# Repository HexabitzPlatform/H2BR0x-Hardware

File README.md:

# H2RB0x-Hardware
Hexabitz Single-Lead, Heart Rate Monitor Front End (based on AD8232) Module Hardware Design

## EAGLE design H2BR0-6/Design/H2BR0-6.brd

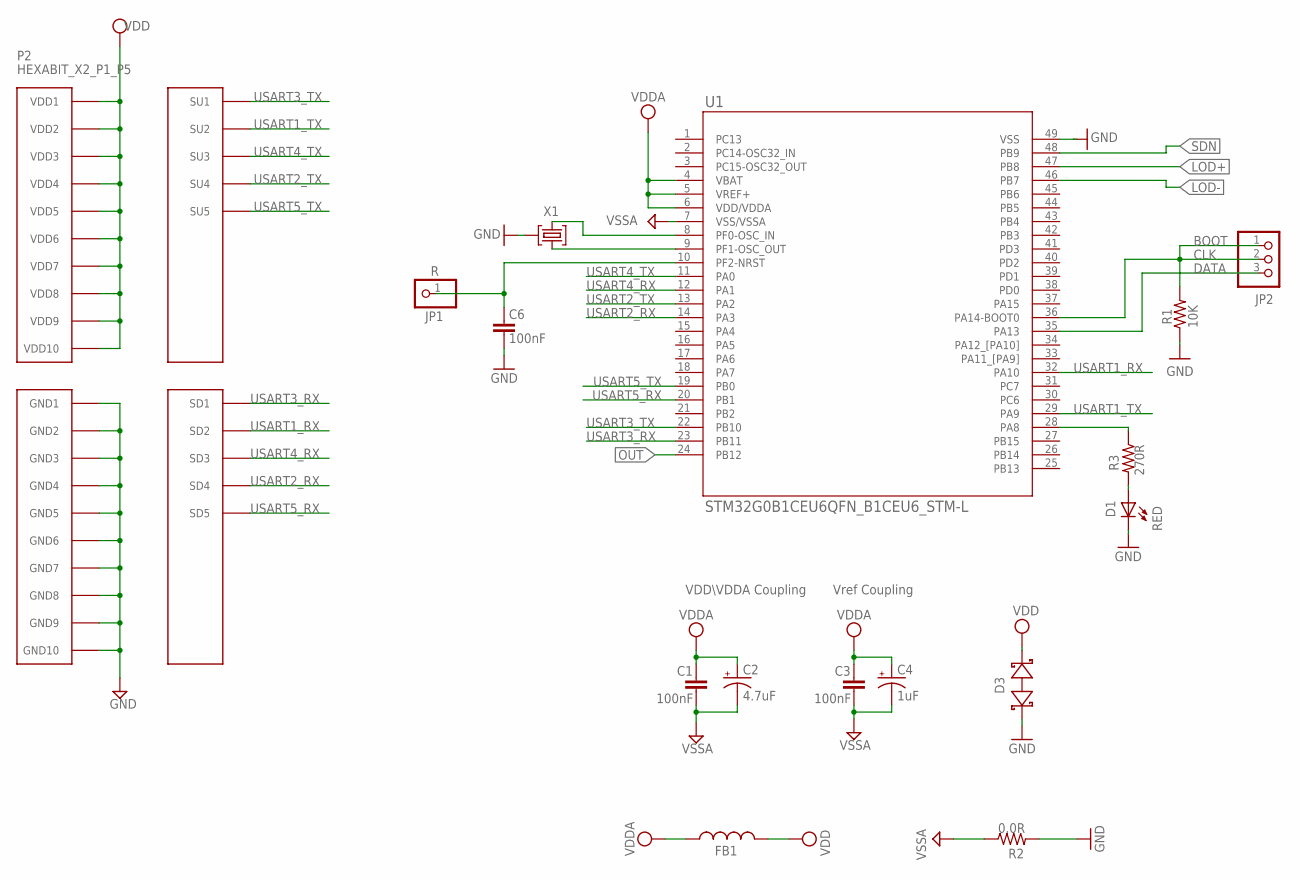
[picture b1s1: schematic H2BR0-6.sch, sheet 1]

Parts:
C1, C3, C6: 100nF; C-0603
C2: 4.7uF; C-0805-POL
C4: 1uF; C-0805-POL
D1: RED; VLMS1300-GS08; MPN VLMS1300-GS08
D3: BOURNS_CDSOD323-T03SCBOURNS_CDSOD323-T03SC_0_0; BOURNS_CDSOD323-T03SC_0
FB1: FB-0603
JP1: R; 1X01
JP2: PINHD-1X3; 1X03
P2: HEXABIT_X2_P1_P5; HEXABIT_17.32_X2_P1_P5
R1: 10K; R-0603
R2: 0.0R; R-0603
R3: 270R; R-0603
TRIMBLE-LOGO2: HEXA-LOGO
U1: STM32G0B1CEU6QFN_B1CEU6_STM-L; QFN_B1CEU6_STM-L
X1: XTALL_CSTCE8M00G52

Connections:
CLK: JP2.1, JP2.2, R1.2, U1.36 (PA14-BOOT0)
DATA: JP2.3, U1.35 (PA13)
GND: C6.2, D1.C, D3.1 (A), P2.PAD_PD11 (GND1), P2.PAD_PD12 (GND2), P2.PAD_PD13 (GND3), P2.PAD_PD14 (GND4), P2.PAD_PD15 (GND5), P2.PAD_PD16 (GND6), P2.PAD_PD17 (GND7), P2.PAD_PD18 (GND8), P2.PAD_PD19 (GND9), P2.PAD_PD20 (GND10), R1.1, R2.2, U1.49 (VSS), X1.P$2 (2)
LOD+: U1.47 (PB8); also elsewhere on the board
LOD-: U1.46 (PB7); also elsewhere on the board
unnamed: D1.A, R3.2
unnamed: R3.1, U1.28 (PA8)
unnamed: U1.9 (PF1-OSC_OUT), X1.P$1 (1)
unnamed: U1.8 (PF0-OSC_IN), X1.P$3 (3)
unnamed: C6.1, JP1.1, U1.10 (PF2-NRST)
OUT: U1.24 (PB12); also elsewhere on the board
SDN: U1.48 (PB9); also elsewhere on the board
USART1_RX: P2.PAD_PD2 (SD2), U1.32 (PA10)
USART1_TX: P2.PAD_PU2 (SU2), U1.29 (PA9)
USART2_RX: P2.PAD_PD4 (SD4), U1.14 (PA3)
USART2_TX: P2.PAD_PU4 (SU4), U1.13 (PA2)
USART3_RX: P2.PAD_PD1 (SD1), U1.23 (PB11)
USART3_TX: P2.PAD_PU1 (SU1), U1.22 (PB10)
USART4_RX: P2.PAD_PD3 (SD3), U1.12 (PA1)
USART4_TX: P2.PAD_PU3 (SU3), U1.11 (PA0)
USART5_RX: P2.PAD_PD5 (SD5), U1.20 (PB1)
USART5_TX: P2.PAD_PU5 (SU5), U1.19 (PB0)
VDD: D3.2 (C), FB1.2, P2.PAD_PU11 (VDD1), P2.PAD_PU12 (VDD2), P2.PAD_PU13 (VDD3), P2.PAD_PU14 (VDD4), P2.PAD_PU15 (VDD5), P2.PAD_PU16 (VDD6), P2.PAD_PU17 (VDD7), P2.PAD_PU18 (VDD8), P2.PAD_PU19 (VDD9), P2.PAD_PU20 (VDD10); also elsewhere on the board
VDDA: C1.1, C2.1 (+), C3.1, C4.1 (+), FB1.1, U1.4 (VBAT), U1.5 (VREF+), U1.6 (VDD/VDDA); also elsewhere on the board
VSSA: C1.2, C2.2 (-), C3.2, C4.2 (-), R2.1, U1.7 (VSS/VSSA); also elsewhere on the board

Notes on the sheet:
Vref Coupling
VDD\VDDA Coupling
BOOT

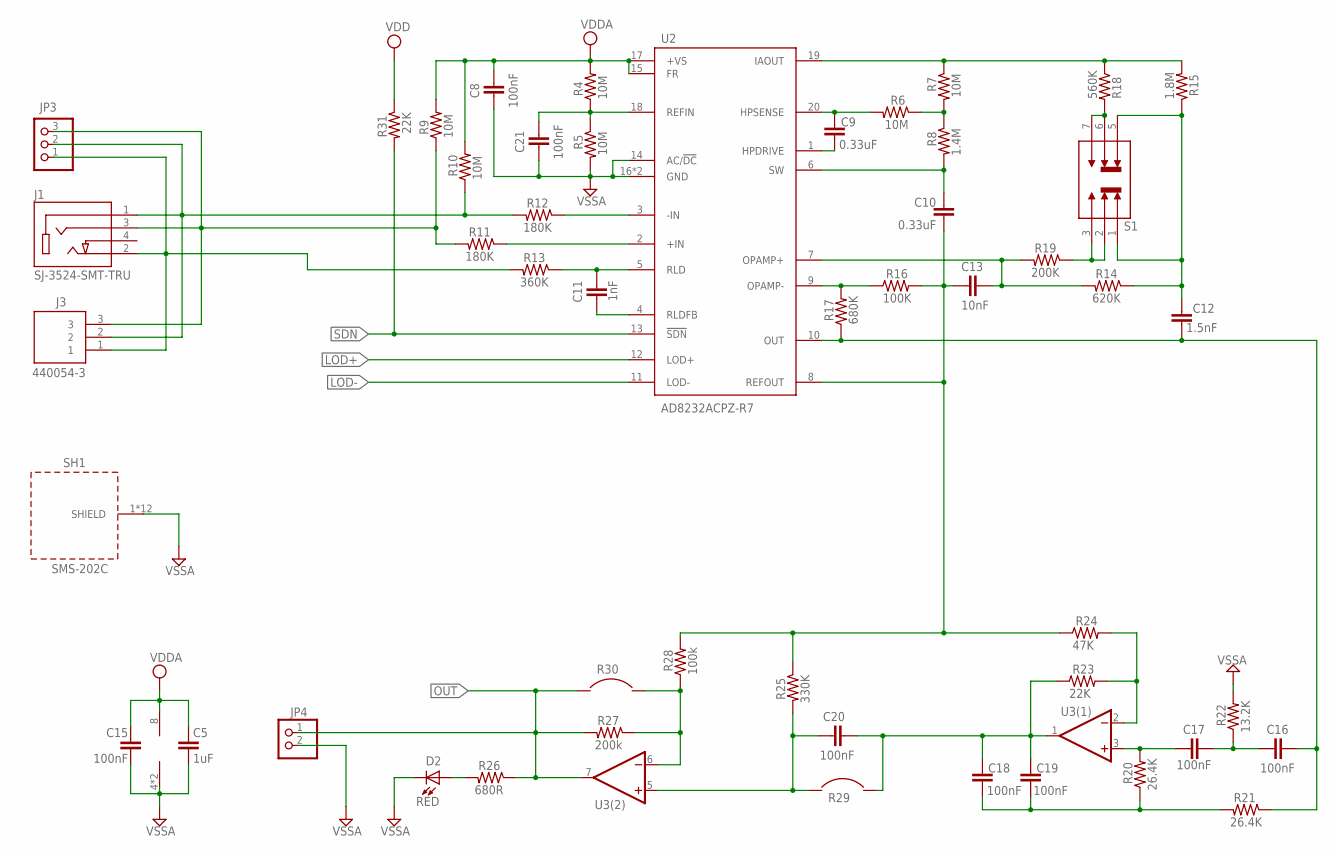
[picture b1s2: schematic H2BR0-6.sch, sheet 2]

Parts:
C5: 1uF; C-0402
C8, C15, C16, C17, C18, C19, C21: 100nF; C-0402
C9, C10: 0.33uF; C-0402
C11: 1nF; C-0402
C12: 1.5nF; C-0402
C13: 10nF; C-0402
C20: 100nF; C-0402; MPN GRM188R61A105KA61J
D2: RED; VLMS1300-GS08; MPN VLMS1300-GS08
J1: SJ-3524-SMT-TRU; CUI_SJ-3524-SMT
J3: 440054-3; SHDR3W50P0X200_1X3_800X470X635
JP3: PINHD-1X3; 1X03
JP4: PINHD-1X2(ROUND); 1X02
R4, R5, R6, R7, R9, R10: 10M; R-0402
R8: 1.4M; R-0402
R11, R12: 180K; R-0402
R13: 360K; R-0402
R14: 620K; R-0402
R15: 1.8M; R-0402
R16: 100K; R-0402
R17: 680K; R-0402
R18: 560K; R-0402
R19: 200K; R-0402
R20, R21: 26.4K; R-0402
R22: 13.2K; R-0402
R23, R31: 22K; R-0402
R24: 47K; R-0402
R25: 330K; R-0402
R26: 680R; R-0603
R27: 200k; R-0402
R28: 100k; R-0402
R29, R30: SB-0603
S1: JS202011JCQN; SW_JS202011JCQN
SH1: SMS-202C; SMS202F
U2: AD8232ACPZ-R7; QFN50P400X400X80-21N
U3: TSV772IQ2T_SEPARATED_SYMBOLSSON50P200X200X60-9N; SON50P200X200X60-9N

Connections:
IN+: J1.3, J3.3, JP3.3, R9.1, R11.2
IN-: J1.1, J3.2, JP3.2, R10.1, R12.2
LOD+: U2.12 (LOD+); also elsewhere on the board
LOD-: U2.11 (LOD-); also elsewhere on the board
unnamed: R16.1, R17.2, U2.9 (OPAMP-)
unnamed: C12.1, C16.2, R17.1, R21.1, U2.10 (OUT)
unnamed: C13.1, R14.2, R19.2, U2.7 (OPAMP+)
unnamed: R27.1, R28.1, R30.2, U3.6 (-IN)
unnamed: R19.1, S1.2, S1.3
unnamed: R18.2, S1.6, S1.7
unnamed: C12.2, R14.1, R15.1, S1.1, S1.5
unnamed: R7.1, R15.2, R18.1, U2.19 (IAOUT)
unnamed: C9.1, R6.2, U2.20 (HPSENSE)
unnamed: C9.2, U2.1 (HPDRIVE)
unnamed: R6.1, R7.2, R8.1
unnamed: R23.2, R24.2, U3.2 (-IN)
unnamed: C21.1, R4.1, R5.1, U2.18 (REFIN)
unnamed: C18.1, C19.1, R20.1, R21.2
unnamed: C11.1, R13.1, U2.5 (RLD)
unnamed: C17.1, R20.2, U3.3 (+IN)
unnamed: C18.2, C19.2, C20.2, R23.1, R29.2, U3.1 (OUT)
unnamed: C16.1, C17.2, R22.1
unnamed: C20.1, R25.2, R29.1, U3.5 (+IN)
unnamed: C10.2, C13.2, R16.2, R24.1, R25.1, R28.2, U2.8 (REFOUT)
unnamed: C10.1, R8.2, U2.6 (SW)
unnamed: D2.A, R26.2
unnamed: C11.2, U2.4 (RLDFB)
unnamed: R12.1, U2.3 (-IN)
unnamed: R11.1, U2.2 (+IN)
OUT: JP4.1, R26.1, R27.2, R30.1, U3.7 (OUT); also elsewhere on the board
REF: J1.2, J3.1, JP3.1, R13.2
SDN: R31.2, U2.13 (!SDN); also elsewhere on the board
VDD: R31.1; also elsewhere on the board
VDDA: C5.1, C8.1, C15.1, R4.2, R9.2, R10.2, U2.15 (FR), U2.17 (+VS), U3.8 (V+); also elsewhere on the board
VSSA: C5.2, C8.2, C15.2, C21.2, D2.C, JP4.2, R5.2, R22.2, SH1.1, SH1.2, SH1.3, SH1.4, SH1.5, SH1.6, SH1.7, SH1.8, SH1.9, SH1.10, SH1.11, SH1.12, U2.14 (AC/!DC), U2.16 (GND), U2.21 (GND), U3.4 (V-), U3.9 (V-); also elsewhere on the board

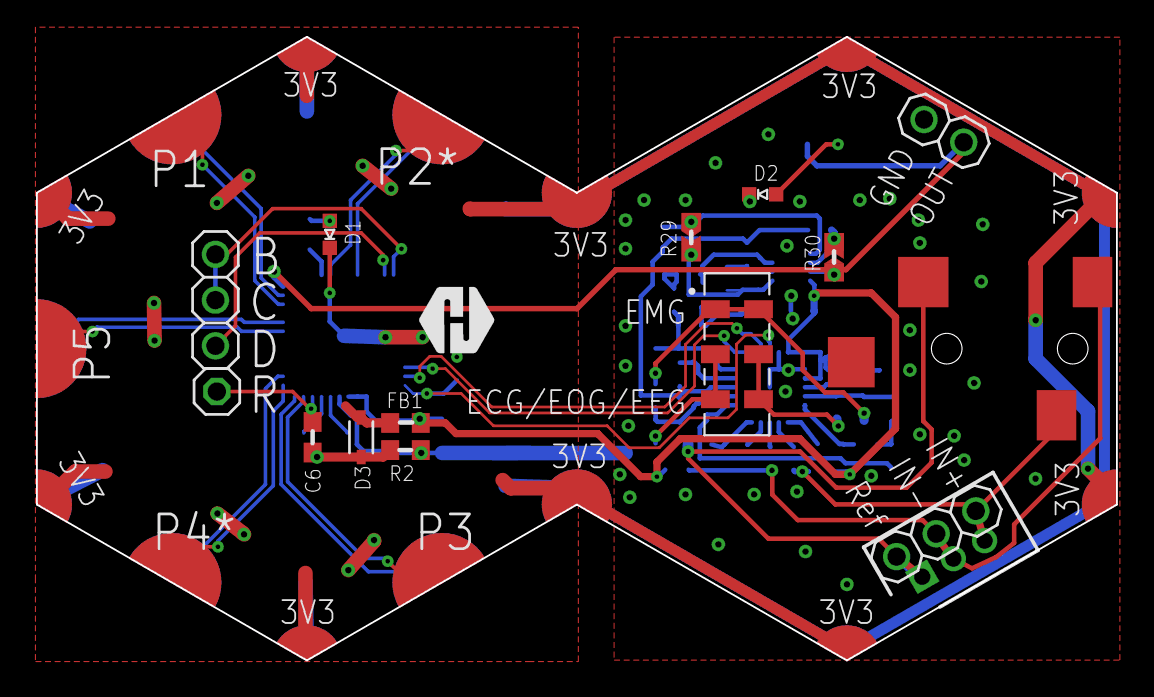
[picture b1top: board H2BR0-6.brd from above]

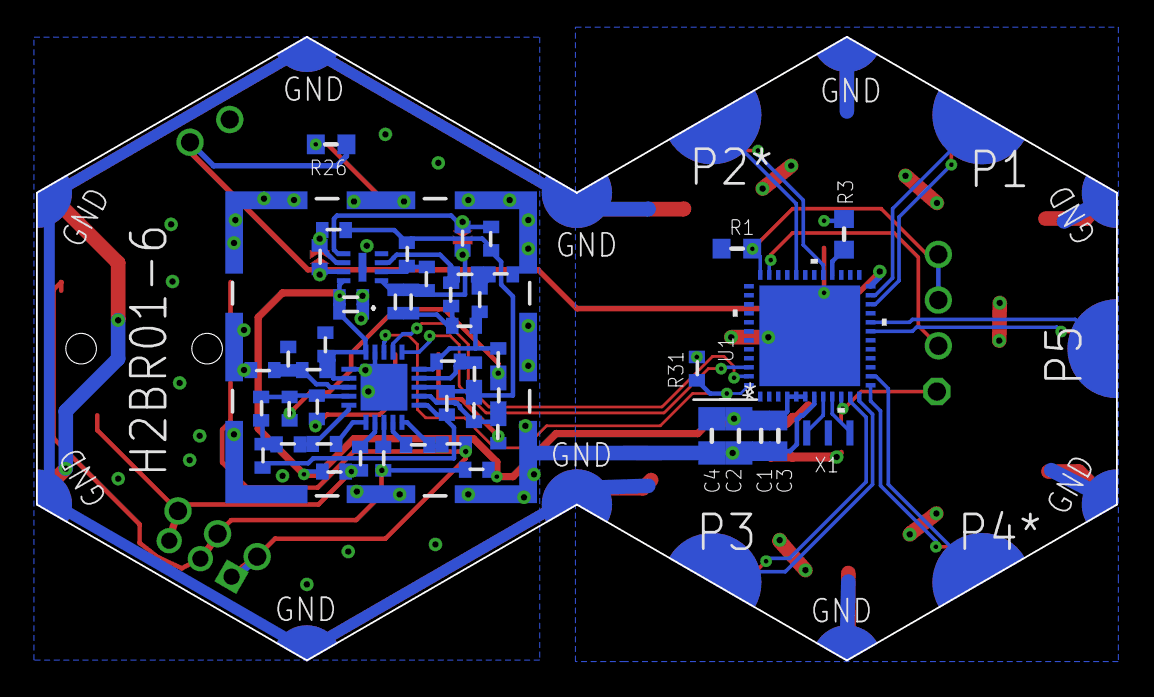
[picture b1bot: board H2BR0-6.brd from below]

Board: 2 copper layers, 60.0 x 34.6 mm, 68 parts (51 on the bottom side), 53 nets.

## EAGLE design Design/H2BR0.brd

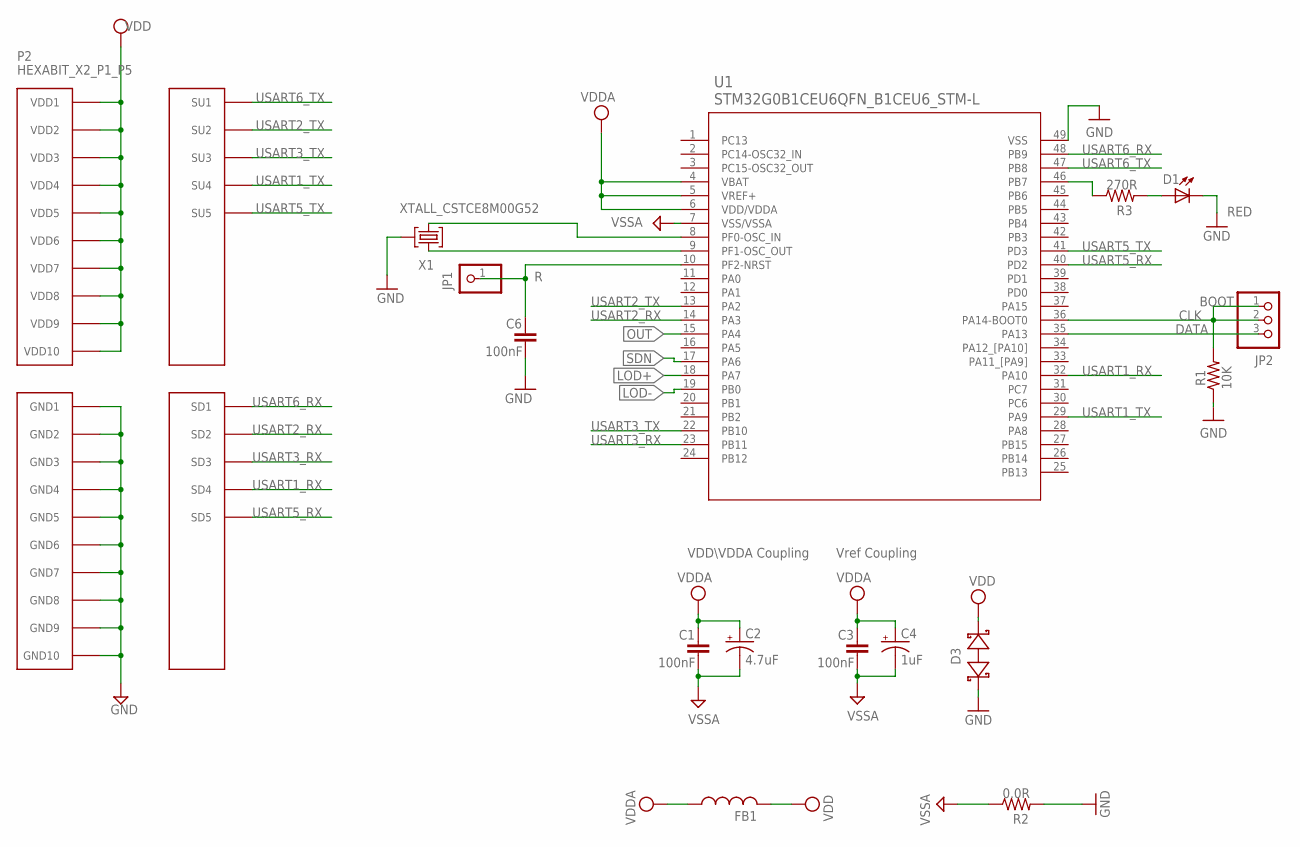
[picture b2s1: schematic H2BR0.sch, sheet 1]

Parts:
C1, C3, C6: 100nF; C-0603
C2: 4.7uF; C-0805-POL
C4: 1uF; C-0805-POL
D1: RED; VLMS1300-GS08; MPN VLMS1300-GS08
D3: BOURNS_CDSOD323-T03SCBOURNS_CDSOD323-T03SC_0_0; BOURNS_CDSOD323-T03SC_0
FB1: FB-0603
JP1: R; 1X01
JP2: PINHD-1X3; 1X03
P2: HEXABIT_X2_P1_P5; HEXABIT_17.32_X2_P1_P5
R1: 10K; R-0603
R2: 0.0R; R-0603
R3: 270R; R-0603
TRIMBLE-LOGO2: HEXA-LOGO
U1: STM32G0B1CEU6QFN_B1CEU6_STM-L; QFN_B1CEU6_STM-L
X1: XTALL_CSTCE8M00G52

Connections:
CLK: JP2.1, JP2.2, R1.2, U1.36 (PA14-BOOT0)
DATA: JP2.3, U1.35 (PA13)
GND: C6.2, D1.C, D3.1 (A), P2.PAD_PD11 (GND1), P2.PAD_PD12 (GND2), P2.PAD_PD13 (GND3), P2.PAD_PD14 (GND4), P2.PAD_PD15 (GND5), P2.PAD_PD16 (GND6), P2.PAD_PD17 (GND7), P2.PAD_PD18 (GND8), P2.PAD_PD19 (GND9), P2.PAD_PD20 (GND10), R1.1, R2.2, U1.49 (VSS), X1.P$2 (2); also elsewhere on the board
LOD+: U1.18 (PA7); also elsewhere on the board
LOD-: U1.19 (PB0); also elsewhere on the board
unnamed: D1.A, R3.2
unnamed: R3.1, U1.46 (PB7)
unnamed: U1.9 (PF1-OSC_OUT), X1.P$1 (1)
unnamed: U1.8 (PF0-OSC_IN), X1.P$3 (3)
unnamed: C6.1, JP1.1, U1.10 (PF2-NRST)
OUT: U1.15 (PA4); also elsewhere on the board
SDN: U1.17 (PA6); also elsewhere on the board
USART1_RX: P2.PAD_PD4 (SD4), U1.32 (PA10)
USART1_TX: P2.PAD_PU4 (SU4), U1.29 (PA9)
USART2_RX: P2.PAD_PD2 (SD2), U1.14 (PA3)
USART2_TX: P2.PAD_PU2 (SU2), U1.13 (PA2)
USART3_RX: P2.PAD_PD3 (SD3), U1.23 (PB11)
USART3_TX: P2.PAD_PU3 (SU3), U1.22 (PB10)
USART5_RX: P2.PAD_PD5 (SD5), U1.40 (PD2)
USART5_TX: P2.PAD_PU5 (SU5), U1.41 (PD3)
USART6_RX: P2.PAD_PD1 (SD1), U1.48 (PB9)
USART6_TX: P2.PAD_PU1 (SU1), U1.47 (PB8)
VDD: D3.2 (C), FB1.2, P2.PAD_PU11 (VDD1), P2.PAD_PU12 (VDD2), P2.PAD_PU13 (VDD3), P2.PAD_PU14 (VDD4), P2.PAD_PU15 (VDD5), P2.PAD_PU16 (VDD6), P2.PAD_PU17 (VDD7), P2.PAD_PU18 (VDD8), P2.PAD_PU19 (VDD9), P2.PAD_PU20 (VDD10)
VDDA: C1.1, C2.1 (+), C3.1, C4.1 (+), FB1.1, U1.4 (VBAT), U1.5 (VREF+), U1.6 (VDD/VDDA); also elsewhere on the board
VSSA: C1.2, C2.2 (-), C3.2, C4.2 (-), R2.1, U1.7 (VSS/VSSA)

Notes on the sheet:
Vref Coupling
VDD\VDDA Coupling
BOOT

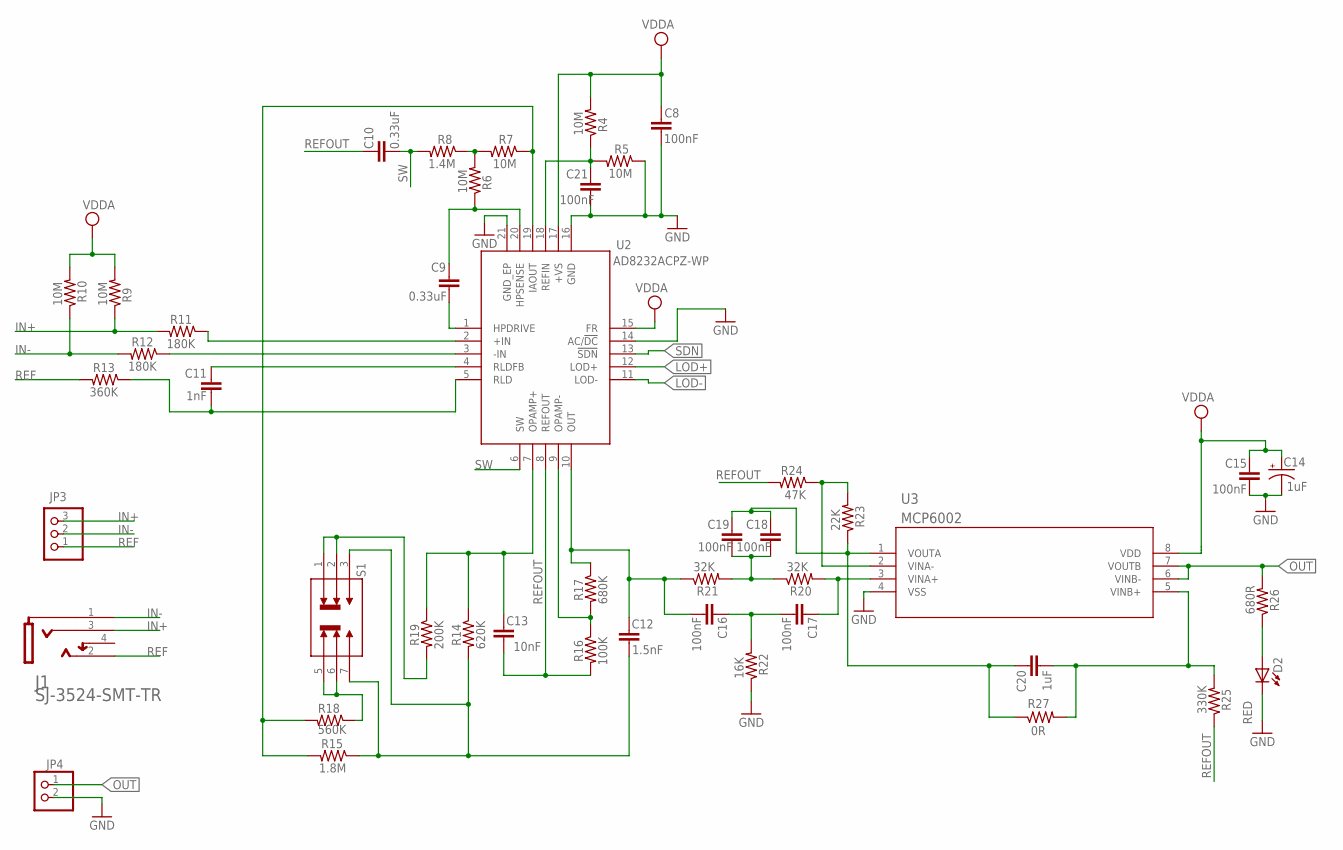
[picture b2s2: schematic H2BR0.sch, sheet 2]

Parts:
C8, C15, C16, C17, C18, C19, C21: 100nF; C-0603
C9, C10: 0.33uF; C-0603
C11: 1nF; C-0603
C12: 1.5nF; C-0603
C13: 10nF; C-0603
C14: 1uF; C-0805-POL
C20: 1uF; C-0603; MPN GRM188R61A105KA61J
D2: RED; VLMS1300-GS08; MPN VLMS1300-GS08
J1: CUI_DEVICES_SJ-3524-SMT-TRCUI_DEVICES_SJ-3524-SMT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; CUI_DEVICES_SJ-3524-SMT-TR_0
JP3: PINHD-1X3; 1X03
JP4: PINHD-1X2(ROUND); 1X02
R4, R5, R6, R7, R9, R10: 10M; R-0603
R8: 1.4M; R-0603
R11, R12: 180K; R-0603
R13: 360K; R-0603
R14: 620K; R-0603
R15: 1.8M; R-0603
R16: 100K; R-0603
R17: 680K; R-0603
R18: 560K; R-0603
R19: 200K; R-0603
R20, R21: 32K; R-0603
R22: 16K; R-0603
R23: 22K; R-0603
R24: 47K; R-0603
R25: 330K; R-0603
R26: 680R; R-0603
R27: 0R; R-0603
S1: JS202011JCQN; SW_JS202011JCQN
U2: AD8232ACPZ-WP; QFN50P400X400X80-21N
U3: MCP6002; SOIC8-N_MC_MCH-L

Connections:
GND: C8.2, C14.2 (-), C15.2, C21.2, D2.C, JP4.2, R5.1, R22.1, U2.14 (AC/!DC), U2.16 (GND), U2.21 (GND_EP), U3.4 (VSS); also elsewhere on the board
IN+: J1.3 (RING), JP3.3, R9.1, R11.2
IN-: J1.1 (SLEEVE), JP3.2, R10.1, R12.2
LOD+: U2.12 (LOD+); also elsewhere on the board
LOD-: U2.11 (LOD-); also elsewhere on the board
unnamed: C21.1, R4.1, R5.2, U2.18 (REFIN)
unnamed: C9.2, U2.1 (HPDRIVE)
unnamed: C9.1, R6.1, U2.20 (HPSENSE)
unnamed: R7.1, R15.2, R18.2, U2.19 (IAOUT)
unnamed: R6.2, R7.2, R8.1
unnamed: R16.1, R17.2, U2.9 (OPAMP-)
unnamed: C12.1, C16.2, R17.1, R21.1, U2.10 (OUT)
unnamed: C11.1, U2.4 (RLDFB)
unnamed: R11.1, U2.2 (+IN)
unnamed: R12.1, U2.3 (-IN)
unnamed: C12.2, R14.2, R15.1, S1.3, S1.7
unnamed: C11.2, R13.1, U2.5 (RLD)
unnamed: C13.1, R14.1, R19.1, U2.7 (OPAMP+)
unnamed: R18.1, S1.5, S1.6
unnamed: R19.2, S1.1, S1.2
unnamed: C17.1, R20.2, U3.3 (VINA+)
unnamed: D2.A, R26.1
unnamed: C16.1, C17.2, R22.2
unnamed: C20.2, R25.2, R27.2, U3.5 (VINB+)
unnamed: C18.1, C19.1, C20.1, R23.1, R27.1, U3.1 (VOUTA)
unnamed: R23.2, R24.1, U3.2 (VINA-)
unnamed: C18.2, C19.2, R20.1, R21.2
OUT: JP4.1, R26.2, U3.6 (VINB-), U3.7 (VOUTB); also elsewhere on the board
REF: J1.2 (TIP), JP3.1, R13.2
REFOUT: C10.1, C13.2, R16.2, R24.2, R25.1, U2.8 (REFOUT)
SDN: U2.13 (!SDN); also elsewhere on the board
SW: C10.2, R8.2, U2.6 (SW)
VDDA: C8.1, C14.1 (+), C15.1, R4.2, R9.2, R10.2, U2.15 (FR), U2.17 (+VS), U3.8 (VDD); also elsewhere on the board

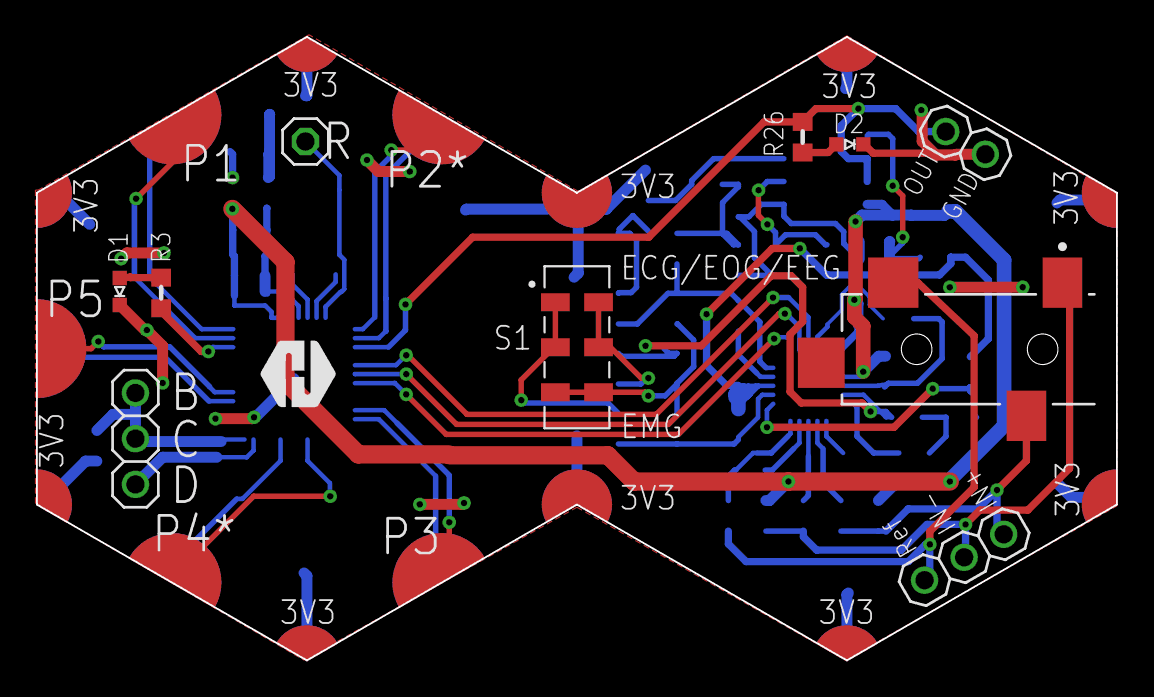
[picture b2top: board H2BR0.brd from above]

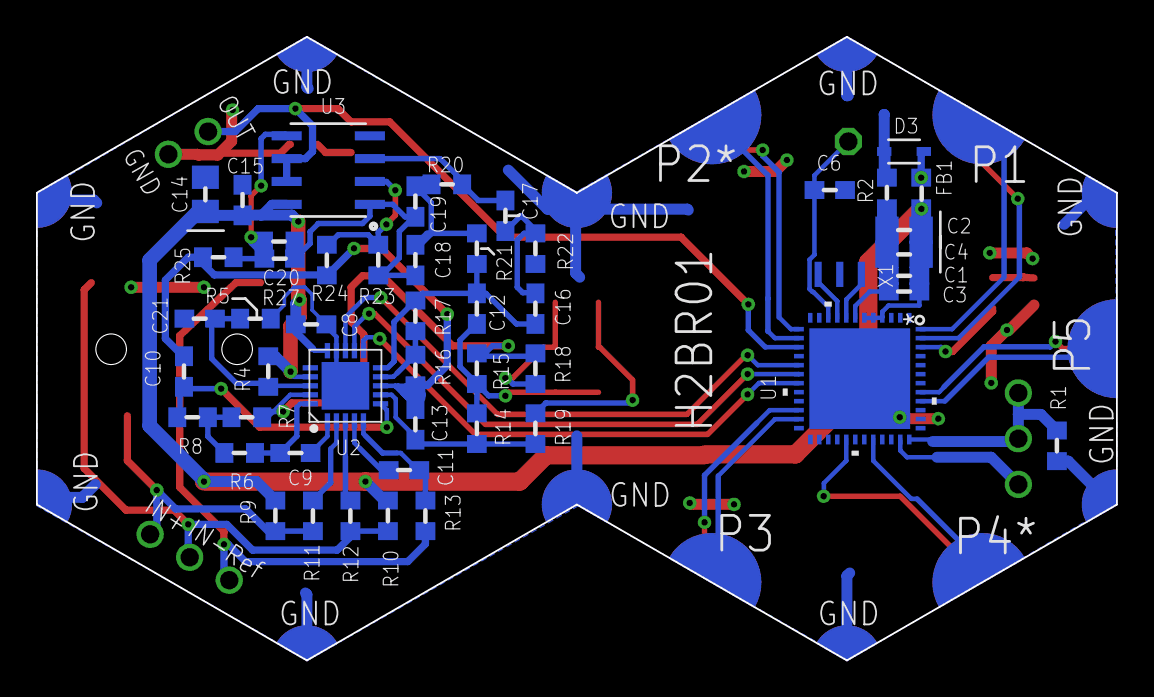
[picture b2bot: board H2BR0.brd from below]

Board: 2 copper layers, 60.0 x 34.6 mm, 62 parts (50 on the bottom side), 52 nets.

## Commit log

2022-08-19 Added .gitignore file
2022-08-23 no message
2022-08-24 Edit Readme file
2022-08-24 Revert "Edit Readme file"
    This reverts commit 2eed6b928030ef120eba9bd8712eb8acb35e65bd.
2023-02-15 -Correcting some documentaion issues
2023-09-23 -Update BOM
2024-07-19 -Add TVS diode -Change the MCU to STM32G0B1CEU6 -Activate the thermal option for the polygon -Update the logo -Add jumber resistor to edit the filter
2025-01-14 -The final design, all done.
2025-01-21 Adding the 60Hz version.

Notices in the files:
parts and their libraries:
COPYRIGHT: Copyright (C) 2021 Ultra Librarian. All rights reserved.
COPYRIGHT: Copyright (C) 2022 Ultra Librarian. All rights reserved.
